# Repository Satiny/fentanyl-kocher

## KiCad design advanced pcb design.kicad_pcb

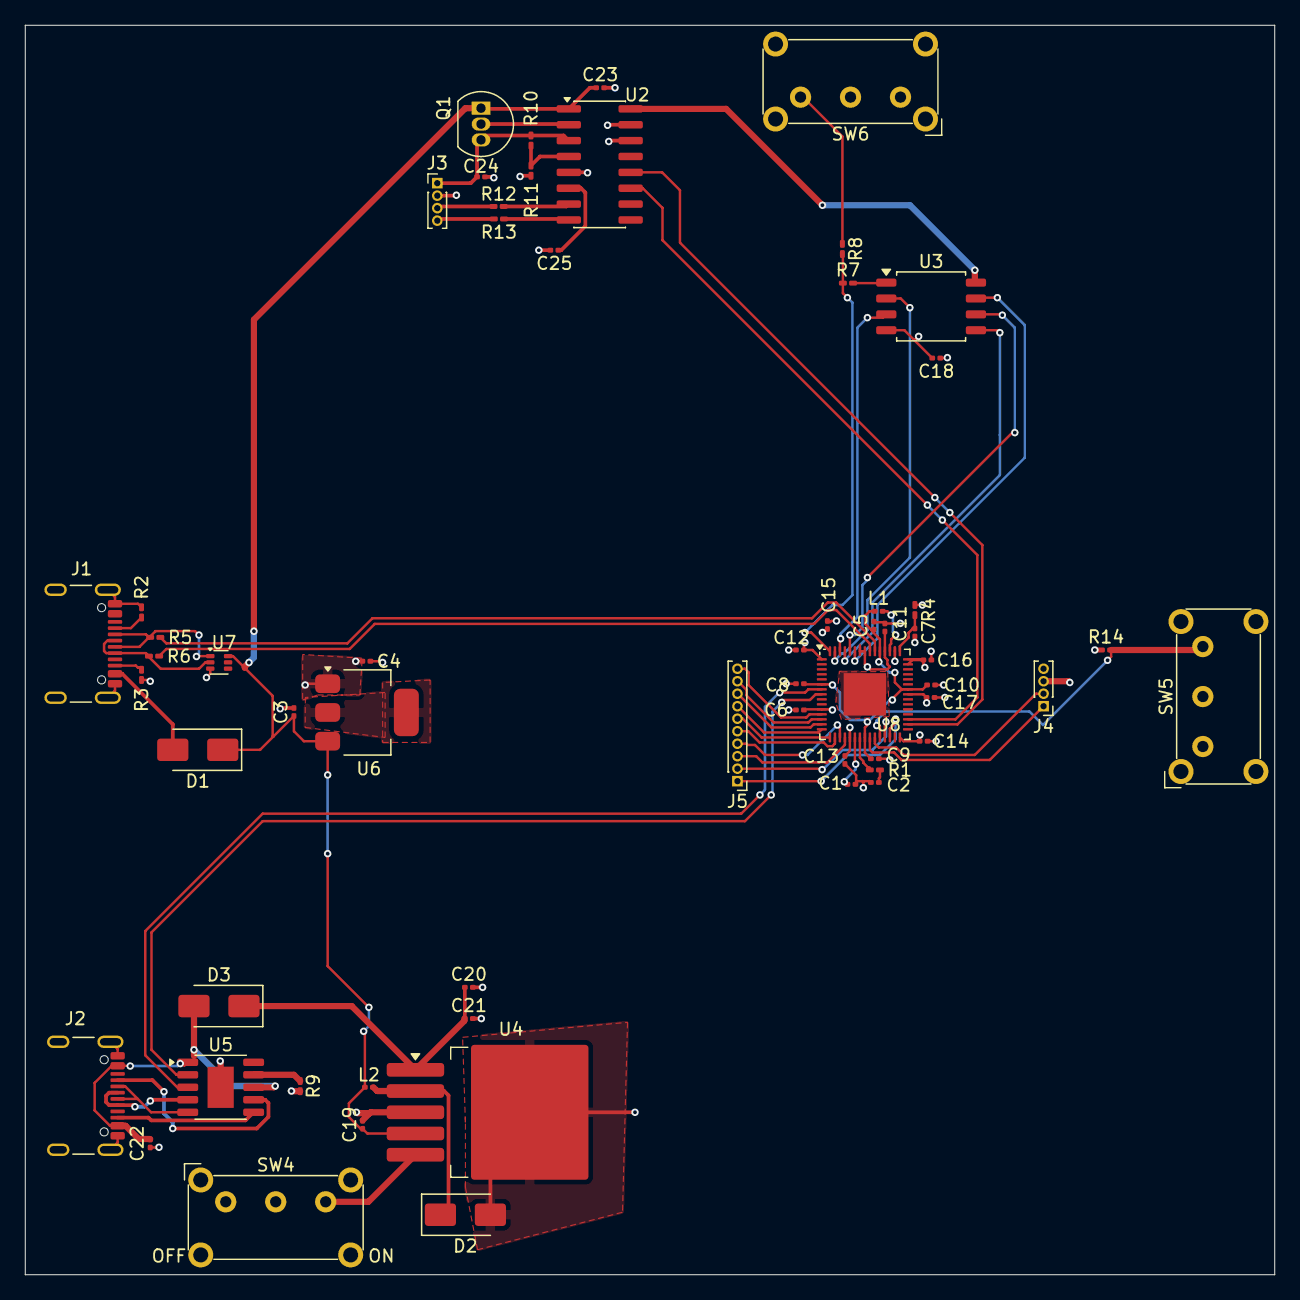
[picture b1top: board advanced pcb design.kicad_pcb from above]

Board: 4 copper layers, 100.0 x 100.0 mm, 60 parts (0 on the bottom side), 58 nets.

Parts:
C1, C2: 15p; C_0201_0603Metric
C3, C23, C24: 10u; C_0201_0603Metric
C4: 22u; C_0201_0603Metric
C5, C6, C7: 4.7u; C_0201_0603Metric
C8, C9, C10, C11, C12, C13, C14, C15, C16, C17, C18, C20: 100n; C_0201_0603Metric
C19: 330u; C_0201_0603Metric
C21: 470u; C_0201_0603Metric
C22: 1u; C_0201_0603Metric
C25: 0.1u; C_0201_0603Metric
D1, D2, D3: SS34; D_SMA
J1, J2: USB_C_Receptacle_USB2.0_16P; USB_C_Receptacle_GCT_USB4105-xx-A_16P_TopMnt_Horizontal
J3, J4: Conn_01x04_Pin; PinHeader_1x04_P1.00mm_Vertical
J5: Conn_01x10_Pin; PinHeader_1x10_P1.00mm_Vertical
L1: 3.3u; L_0201_0603Metric
L2: 33u; L_0201_0603Metric
Q1: S8550; TO-92_Inline
R1, R8: 1k; R_0201_0603Metric_Pad0.64x0.40mm_HandSolder
R2, R3: 5.1k; R_0201_0603Metric_Pad0.64x0.40mm_HandSolder
R4: 33; R_0201_0603Metric_Pad0.64x0.40mm_HandSolder
R5, R6: 27; R_0201_0603Metric_Pad0.64x0.40mm_HandSolder
R7: 0; R_0201_0603Metric_Pad0.64x0.40mm_HandSolder
R9: 24k; R_0201_0603Metric_Pad0.64x0.40mm_HandSolder
R10: 20k; R_0201_0603Metric_Pad0.64x0.40mm_HandSolder
R11: 8.2k; R_0201_0603Metric_Pad0.64x0.40mm_HandSolder
R12, R13: 100; R_0201_0603Metric_Pad0.64x0.40mm_HandSolder
R14: 10k; R_0201_0603Metric_Pad0.64x0.40mm_HandSolder
SW4, SW5, SW6: SW_MEC_5G; SW_E-Switch_EG1224_SPDT_Angled
U2: HX711; SOIC-16_3.9x9.9mm_P1.27mm
U3: W25Q128JVS; SOIC-8_5.3x5.3mm_P1.27mm
U4: LM2596S-5; TO-263-5_TabPin3
U5: CH224Q; SSOP-10-1EP_3.9x4.9mm_P1mm_EP2.1x3.3mm
U6: AMS1117-3.3; SOT-223-3_TabPin2
U7: TPD4E1U06; SOT-563
U8: RP2350A; QFN-60-1EP_7x7mm_P0.4mm_EP3.4x3.4mm

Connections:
+1.1V: C5.1, C8.1, C9.1, C10.1, L1.1, U8.6 (DVDD), U8.23 (DVDD), U8.39 (DVDD), U8.50 (VREG_FB)
+3.3V: C4.1, C6.1, C11.1, C12.1, C13.1, C14.1, C15.1, C16.1, C17.1, C18.1, J4.4, R4.1, R14.1, U2.16 (DVDD), U3.8 (VCC), U6.2 (VO), U8.1 (IOVDD), U8.11 (IOVDD), U8.20 (IOVDD), U8.30 (IOVDD), U8.38 (IOVDD), U8.44 (ADC_AVDD), U8.45 (IOVDD), U8.49 (VREG_VIN), U8.53 (USB_OTP_VDD), U8.54 (QSPI_IOVDD)
+5V: C3.1, C19.1, C23.1, D1.1 (K), L2.2, Q1.1 (E), U2.1 (VSUP), U4.4 (FB), U6.3 (VI), U7.6 (V_{cc})
+12V: C20.1, C21.1, D3.1 (K), U4.1 (VIN)
/CFG2/SCL: U5.2 (CFG2), U8.8 (GPIO5)
/CFG3/SDA: U5.3 (CFG3), U8.7 (GPIO4)
/DOUT: U2.12 (DOUT), U8.32 (GPIO20)
/PD_SCK: U2.11 (PD_SCK), U8.33 (GPIO21)
/QSPI_SD0: U3.5 (DI/IO_{0}), U8.57 (QSPI_SD0)
/QSPI_SD1: U3.2 (DO/IO_{1}), U8.59 (QSPI_SD1)
/QSPI_SD2: U3.3 (~WP/IO_{2}), U8.58 (QSPI_SD2)
/QSPI_SD3: U3.7 (~HOLD/~RESET/IO_{3}), U8.55 (QSPI_SD3)
/QSPI_SS: R7.1, R8.2, U8.60 (~QSPI_SS)
/SPI_SCLK: U3.6 (CLK), U8.56 (QSPI_SCLK)
/USB+: R6.2, U8.52 (USB_DP)
/USB-: R5.1, U8.51 (USB_DM)
GND: C1.1, C2.1, C3.2, C4.2, C5.2, C6.2, C7.1, C8.2, C9.2, C10.2, C11.2, C12.2, C13.2, C14.2, C15.2, C16.2, C17.2, C18.2, C19.2, C20.2, C21.2, C22.1, C23.2, C24.2, C25.2, D2.2 (A), J1.A1 (GND), J1.A12 (GND), J1.B1 (GND), J1.B12 (GND), J1.SH (SHIELD), J2.A1 (GND), J2.A12 (GND), J2.B1 (GND), J2.B12 (GND), J2.SH (SHIELD), J3.2, J4.3, R2.1, R3.2, R9.2, R11.2, SW4.1 (A), SW4.2 (A), SW5.1 (A), SW5.2 (A), SW6.1 (A), SW6.2 (A), U2.5 (AGND), U2.14 (XI), U2.15 (RATE), U3.4 (GND), U4.3 (GND), U5.11 (GND), U6.1 (GND), U7.3 (GND), U8.47 (VREG_PGND), U8.61 (GND)
unnamed: C2.2, R1.1
unnamed: D1.2 (A), J1.A4 (VBUS), J1.A9 (VBUS), J1.B4 (VBUS), J1.B9 (VBUS)
unnamed: D2.1 (K), L2.1, U4.2 (OUT)
unnamed: C22.2, D3.2 (A), J2.A4 (VBUS), J2.A9 (VBUS), J2.B4 (VBUS), J2.B9 (VBUS), U5.1 (VHV), U5.8 (VBUS)
unnamed: J1.A5 (CC1), R2.2
unnamed: J1.B5 (CC2), R3.1
unnamed: J2.A5 (CC1), U5.7 (CC1)
unnamed: J2.B5 (CC2), U5.6 (CC2)
unnamed: C24.1, J3.1, Q1.3 (C), R10.1, U2.3 (AVDD)
unnamed: J3.3, R12.2
unnamed: J3.4, R13.2
unnamed: J4.1, U8.24 (SWCLK)
unnamed: J4.2, U8.25 (SWDIO)
unnamed: J5.1, U8.28 (GPIO17)
unnamed: J5.2, U8.27 (GPIO16)
unnamed: J5.3, U8.19 (GPIO15)
unnamed: J5.4, U8.18 (GPIO14)
unnamed: J5.5, U8.17 (GPIO13)
unnamed: J5.6, U8.16 (GPIO12)
unnamed: J5.7, U8.15 (GPIO11)
unnamed: J5.8, U8.14 (GPIO10)
unnamed: J5.9, U8.13 (GPIO9)
unnamed: J5.10, U8.12 (GPIO8)
unnamed: Q1.2 (B), U2.2 (BASE)
unnamed: R8.1, SW6.3 (B)
unnamed: R13.1, U2.8 (INA+)
unnamed: R12.1, U2.7 (INA-)
unnamed: C25.1, U2.6 (VBG)
unnamed: R10.2, R11.1, U2.4 (VFB)
unnamed: R7.2, U3.1 (~CS)
unnamed: SW4.3 (B), U4.5 (~ON/OFF)
unnamed: R9.1, U5.9 (CFG1)
unnamed: J2.A7 (D-), J2.B7 (D-), U5.5 (DM)
unnamed: J2.A6 (D+), J2.B6 (D+), U5.4 (DP)
unnamed: J1.A7 (D-), J1.B7 (D-), R5.2, U7.1 (IO1)
unnamed: J1.A6 (D+), J1.B6 (D+), R6.1, U7.2 (IO2)
unnamed: R14.2, SW5.3 (B), U8.26 (RUN)
unnamed: C7.2, R4.2, U8.46 (VREG_AVDD)
unnamed: L1.2, U8.48 (VREG_LX)
unnamed: C1.2, U8.21 (XIN)
unnamed: R1.2, U8.22 (XOUT)
